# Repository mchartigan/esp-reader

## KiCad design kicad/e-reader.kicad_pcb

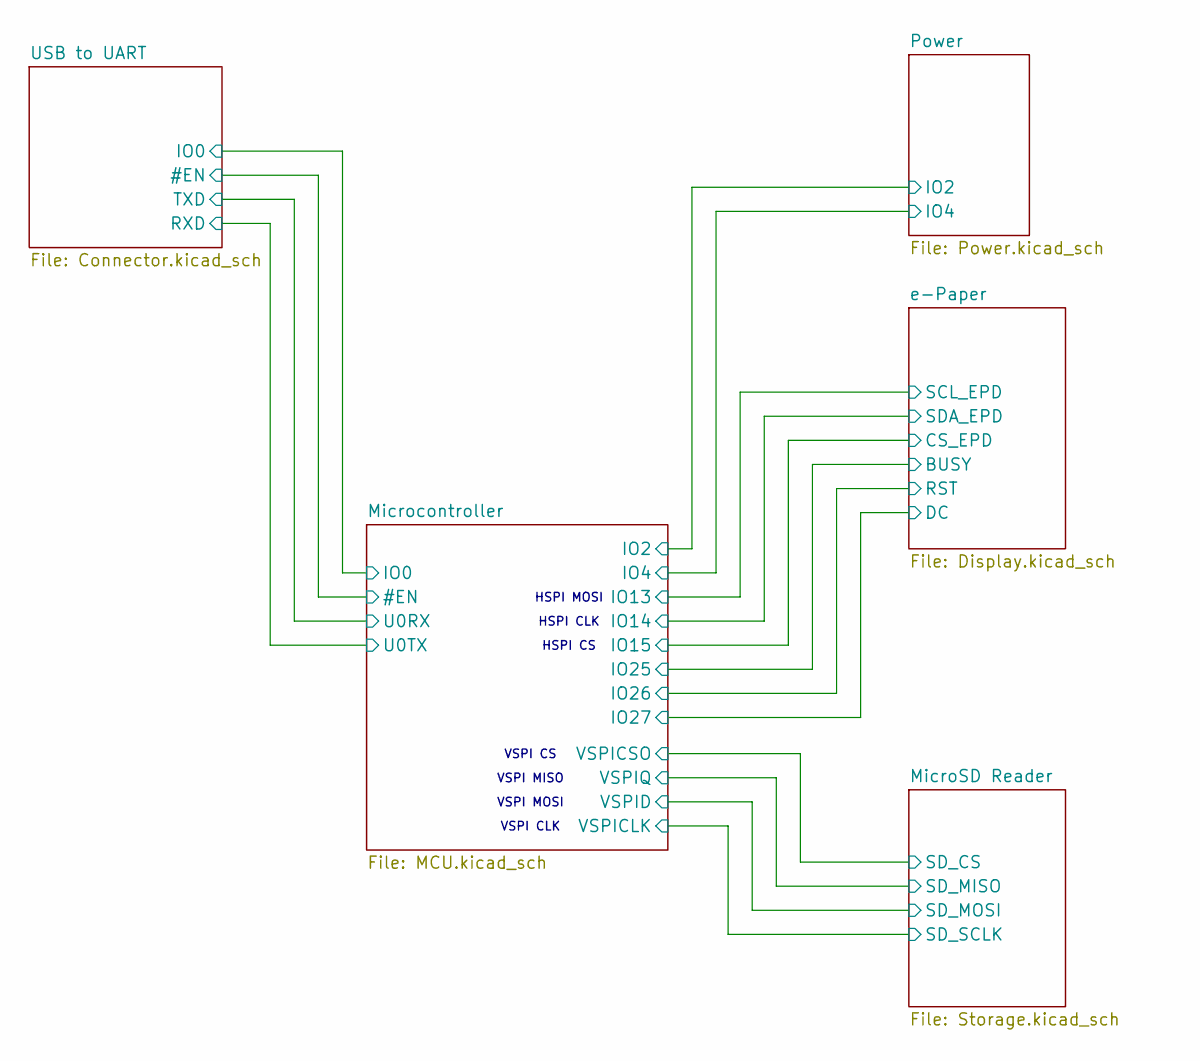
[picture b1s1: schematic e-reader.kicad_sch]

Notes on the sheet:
VSPI CS
VSPI CLK
HSPI CS
VSPI MOSI
HSPI CLK
HSPI MOSI
VSPI MISO

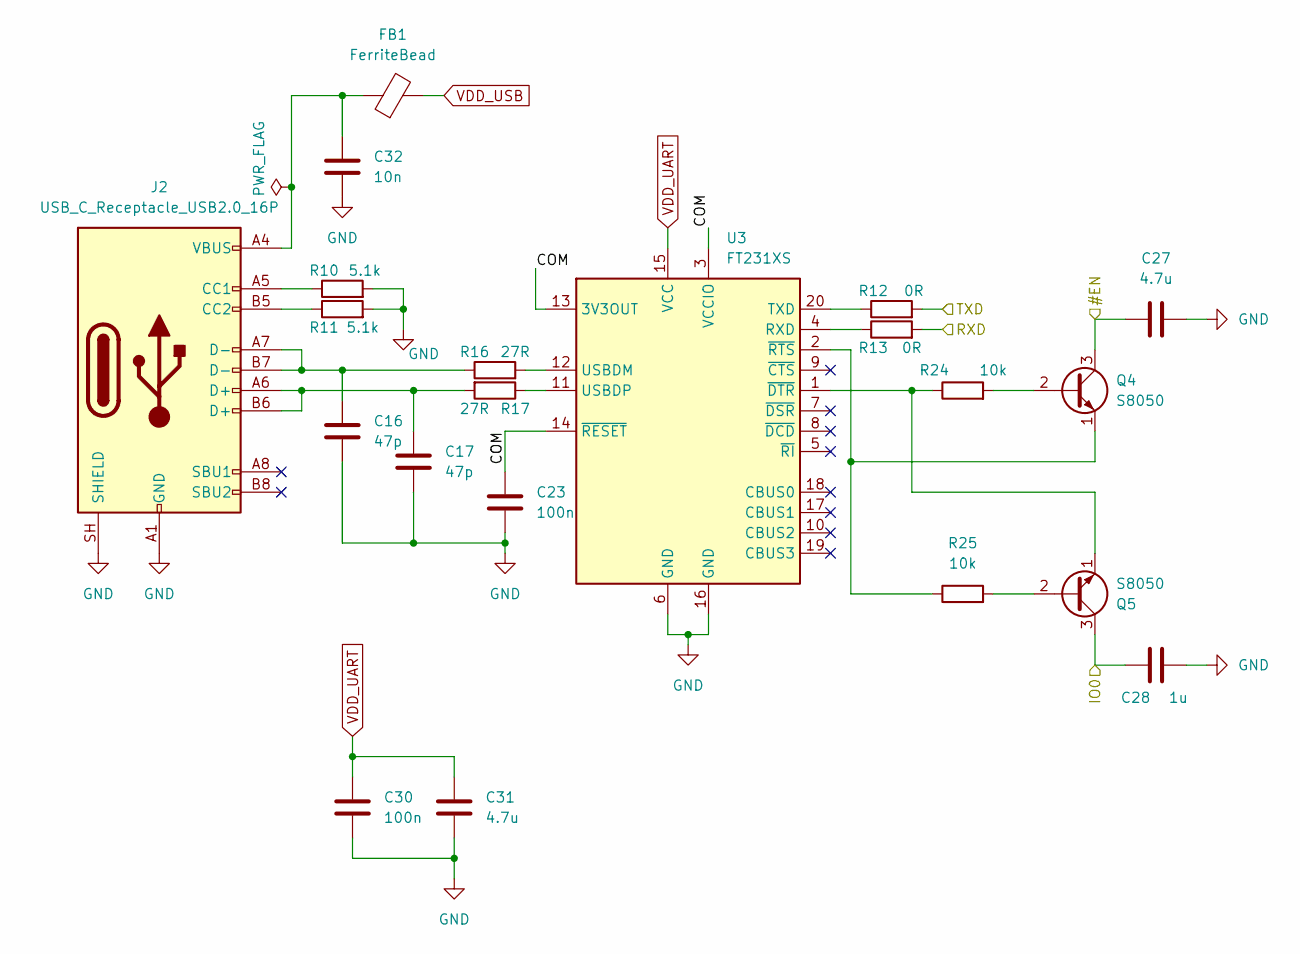
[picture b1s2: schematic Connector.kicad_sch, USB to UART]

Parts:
C16, C17: 47p; C_0603_1608Metric_Pad1.08x0.95mm_HandSolder
C23, C30: 100n; C_0603_1608Metric_Pad1.08x0.95mm_HandSolder
C27, C31: 4.7u; C_0603_1608Metric_Pad1.08x0.95mm_HandSolder
C28: 1u; C_0603_1608Metric_Pad1.08x0.95mm_HandSolder
C32: 10n; C_0603_1608Metric_Pad1.08x0.95mm_HandSolder
FB1: FerriteBead; R_0805_2012Metric_Pad1.20x1.40mm_HandSolder
J2: USB_C_Receptacle_USB2.0_16P; USB_C_Receptacle_GCT_USB4085
Q4, Q5: S8050; TO-92_Inline
R10, R11: 5.1k; R_0603_1608Metric_Pad0.98x0.95mm_HandSolder
R12, R13: 0R; R_0603_1608Metric_Pad0.98x0.95mm_HandSolder
R16, R17: 27R; R_0603_1608Metric_Pad0.98x0.95mm_HandSolder
R24, R25: 10k; R_0603_1608Metric_Pad0.98x0.95mm_HandSolder
U3: FT231XS; SSOP-20_3.9x8.7mm_P0.635mm

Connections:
/Microcontroller/FL_1: C28.1, Q5.3 (C); also elsewhere on the board
/Microcontroller/RST_1: C27.1, Q4.3 (C); also elsewhere on the board
/Microcontroller/U0RX: R12.2; also elsewhere on the board
/Microcontroller/U0TX: R13.2; also elsewhere on the board
/USB to UART/COM: C23.1, U3.3 (VCCIO), U3.13 (3V3OUT), U3.14 (~RESET)
GND: C16.2, C17.2, C23.2, C27.2, C28.2, C30.2, C31.2, C32.2, J2.A1 (GND), J2.A12 (GND), J2.B1 (GND), J2.B12 (GND), J2.SH (SHIELD), R10.2, R11.2, U3.6 (GND), U3.16 (GND); also elsewhere on the board
unnamed: C16.1, J2.A7 (D-), J2.B7 (D-), R16.1
unnamed: C17.1, J2.A6 (D+), J2.B6 (D+), R17.2
unnamed: C32.1, FB1.1, J2.A4 (VBUS), J2.A9 (VBUS), J2.B4 (VBUS), J2.B9 (VBUS)
unnamed: J2.A5 (CC1), R10.1
unnamed: J2.B5 (CC2), R11.1
unnamed: Q4.2 (B), R24.2
unnamed: Q4.1 (E), R25.1, U3.2 (~RTS)
unnamed: Q5.2 (B), R25.2
unnamed: Q5.1 (E), R24.1, U3.1 (~DTR)
unnamed: R13.1, U3.4 (RXD)
unnamed: R12.1, U3.20 (TXD)
unnamed: R16.2, U3.12 (USBDM)
unnamed: R17.1, U3.11 (USBDP)
VDD_UART: C30.1, C31.1, U3.15 (VCC); also elsewhere on the board
VDD_USB: FB1.2; also elsewhere on the board

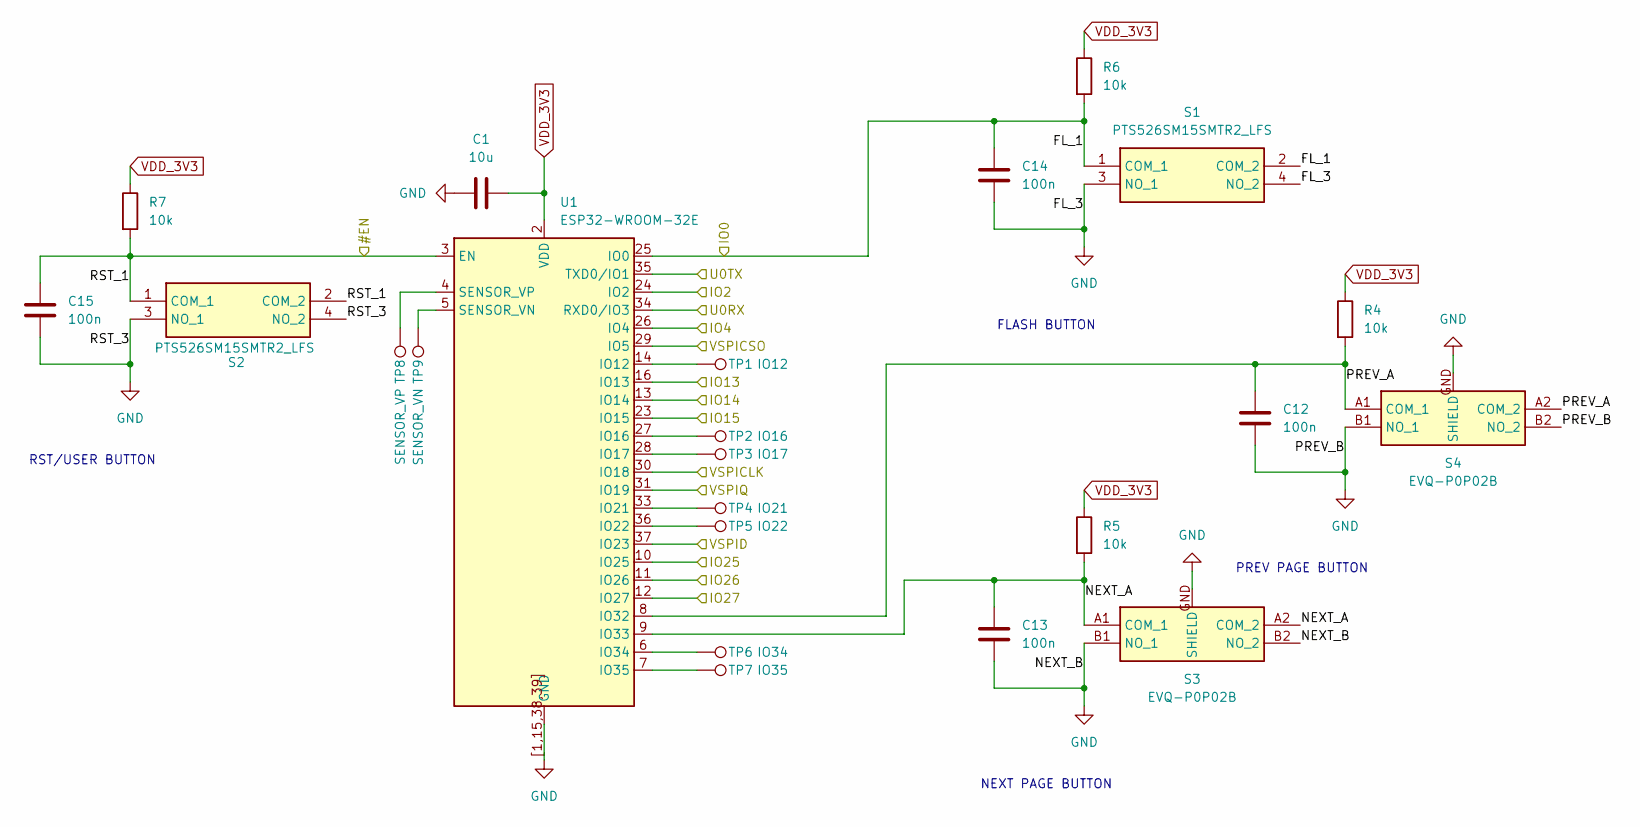
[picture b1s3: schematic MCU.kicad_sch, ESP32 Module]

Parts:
C1: 10u; C_0603_1608Metric_Pad1.08x0.95mm_HandSolder
C12, C13, C14, C15: 100n; C_0603_1608Metric_Pad1.08x0.95mm_HandSolder
R4, R5, R6, R7: 10k; R_0603_1608Metric_Pad0.98x0.95mm_HandSolder
S1, S2: PTS526SM15SMTR2_LFS; PTS526SM15SMTR2LFS; Manufacturer_Part_Number PTS526SM15SMTR2 LFS; Mouser Part Number 611-PTS526SM15SMTR2L
S3, S4: EVQ-P0P02B; EVQP0P02B; Manufacturer_Part_Number EVQ-P0P02B; Mouser Part Number 667-EVQ-P0P02B
TP1: IO12; TestPoint_THTPad_D2.0mm_Drill1.0mm
TP2: IO16; TestPoint_THTPad_D2.0mm_Drill1.0mm
TP3: IO17; TestPoint_THTPad_D2.0mm_Drill1.0mm
TP4: IO21; TestPoint_THTPad_D2.0mm_Drill1.0mm
TP5: IO22; TestPoint_THTPad_D2.0mm_Drill1.0mm
TP6: IO34; TestPoint_THTPad_D2.0mm_Drill1.0mm
TP7: IO35; TestPoint_THTPad_D2.0mm_Drill1.0mm
TP8: SENSOR_VP; TestPoint_THTPad_D2.0mm_Drill1.0mm
TP9: SENSOR_VN; TestPoint_THTPad_D2.0mm_Drill1.0mm
U1: ESP32-WROOM-32E

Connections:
/MicroSD Reader/SD_CS: U1.29 (IO5); also elsewhere on the board
/MicroSD Reader/SD_MISO: U1.31 (IO19); also elsewhere on the board
/MicroSD Reader/SD_MOSI: U1.37 (IO23); also elsewhere on the board
/MicroSD Reader/SD_SCLK: U1.30 (IO18); also elsewhere on the board
/Microcontroller/FL_1: C14.1, R6.2, S1.1 (COM_1), S1.2 (COM_2), U1.25 (IO0); also elsewhere on the board
/Microcontroller/IO2: U1.24 (IO2); also elsewhere on the board
/Microcontroller/IO4: U1.26 (IO4); also elsewhere on the board
/Microcontroller/IO13: U1.16 (IO13); also elsewhere on the board
/Microcontroller/IO14: U1.13 (IO14); also elsewhere on the board
/Microcontroller/IO15: U1.23 (IO15); also elsewhere on the board
/Microcontroller/IO25: U1.10 (IO25); also elsewhere on the board
/Microcontroller/IO26: U1.11 (IO26); also elsewhere on the board
/Microcontroller/IO27: U1.12 (IO27); also elsewhere on the board
/Microcontroller/NEXT_A: C13.1, R5.2, S3.A1 (COM_1), S3.A2 (COM_2), U1.9 (IO33)
/Microcontroller/PREV_A: C12.1, R4.2, S4.A1 (COM_1), S4.A2 (COM_2), U1.8 (IO32)
/Microcontroller/RST_1: C15.1, R7.2, S2.1 (COM_1), S2.2 (COM_2), U1.3 (EN); also elsewhere on the board
/Microcontroller/U0RX: U1.34 (RXD0/IO3); also elsewhere on the board
/Microcontroller/U0TX: U1.35 (TXD0/IO1); also elsewhere on the board
GND: C1.1, C12.2, C13.2, C14.2, C15.2, S1.3 (NO_1), S1.4 (NO_2), S2.3 (NO_1), S2.4 (NO_2), S3.B1 (NO_1), S3.B2 (NO_2), S3.GND (SHIELD), S4.B1 (NO_1), S4.B2 (NO_2), S4.GND (SHIELD), U1.1 (GND), U1.15 (GND), U1.38 (GND), U1.39 (GND), U1.[1,15,38,39] (GND); also elsewhere on the board
unnamed: TP1.1 (1_1), U1.14 (IO12)
unnamed: TP2.1 (1_1), U1.27 (IO16)
unnamed: TP3.1 (1_1), U1.28 (IO17)
unnamed: TP4.1 (1_1), U1.33 (IO21)
unnamed: TP5.1 (1_1), U1.36 (IO22)
unnamed: TP6.1 (1_1), U1.6 (IO34)
unnamed: TP7.1 (1_1), U1.7 (IO35)
unnamed: TP9.1 (1_1), U1.5 (SENSOR_VN)
unnamed: TP8.1 (1_1), U1.4 (SENSOR_VP)
VDD_3V3: C1.2, R4.1, R5.1, R6.1, R7.1, U1.2 (VDD); also elsewhere on the board

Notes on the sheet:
RST/USER BUTTON
NEXT PAGE BUTTON
FLASH BUTTON
PREV PAGE BUTTON

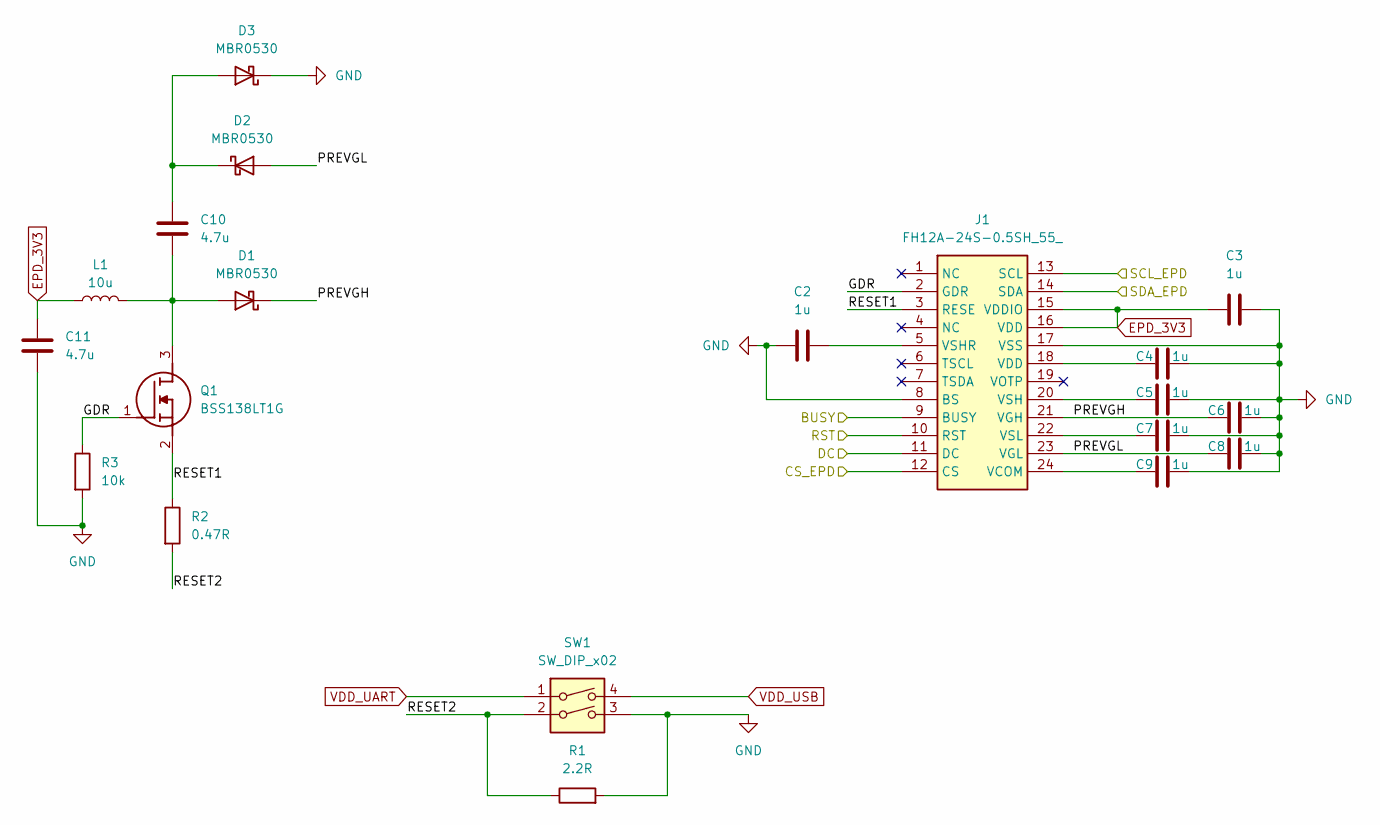
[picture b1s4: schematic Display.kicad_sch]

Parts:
C2, C3, C4, C5, C6, C7, C8, C9: 1u; C_0603_1608Metric_Pad1.08x0.95mm_HandSolder; Voltage 50V
C10: 4.7u; C_0603_1608Metric_Pad1.08x0.95mm_HandSolder; Voltage 50V
C11: 4.7u; C_0603_1608Metric_Pad1.08x0.95mm_HandSolder
D1, D2, D3: MBR0530; D_SOD-123
J1: FH12A-24S-0.5SH_55_; FH12A-24S-0.5SH; Manufacturer_Part_Number FH12A-24S-0.5SH(55); Mouser Part Number 798-FH12A-24S0.5SH55
L1: 10u; SRN4012BTA100M
Q1: BSS138LT1G; Manufacturer_Part_Number BSS138LT1G; Mouser Part Number 863-BSS138LT1G
R1: 2.2R; R_0603_1608Metric_Pad0.98x0.95mm_HandSolder
R2: 0.47R; R_0603_1608Metric_Pad0.98x0.95mm_HandSolder
R3: 10k; R_0603_1608Metric_Pad0.98x0.95mm_HandSolder
SW1: SW_DIP_x02; 2182LPST

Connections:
/Microcontroller/IO13: J1.13 (SCL); also elsewhere on the board
/Microcontroller/IO14: J1.14 (SDA); also elsewhere on the board
/Microcontroller/IO15: J1.12 (CS); also elsewhere on the board
/Microcontroller/IO25: J1.9 (BUSY); also elsewhere on the board
/Microcontroller/IO26: J1.10 (RST); also elsewhere on the board
/Microcontroller/IO27: J1.11 (DC); also elsewhere on the board
/e-Paper/GDR: J1.2 (GDR), Q1.1 (G), R3.1
/e-Paper/PREVGH: C6.1, D1.1 (K), J1.21 (VGH)
/e-Paper/PREVGL: C8.1, D2.2 (A), J1.23 (VGL)
/e-Paper/RESET1: J1.3 (RESE), Q1.2 (S), R2.1
/e-Paper/RESET2: R1.1, R2.2, SW1.2
EPD_3V3: C3.1, C11.1, J1.15 (VDDIO), J1.16 (VDD), L1.1; also elsewhere on the board
GND: C2.1, C3.2, C4.2, C5.2, C6.2, C7.2, C8.2, C9.2, C11.2, D3.1 (K), J1.8 (BS), J1.17 (VSS), R1.2, R3.2, SW1.3; also elsewhere on the board
unnamed: C4.1, J1.18 (VDD)
unnamed: C10.2, D1.2 (A), L1.2, Q1.3 (D)
unnamed: C10.1, D2.1 (K), D3.2 (A)
unnamed: C9.1, J1.24 (VCOM)
unnamed: C5.1, J1.20 (VSH)
unnamed: C2.2, J1.5 (VSHR)
unnamed: C7.1, J1.22 (VSL)
VDD_UART: SW1.1; also elsewhere on the board
VDD_USB: SW1.4; also elsewhere on the board

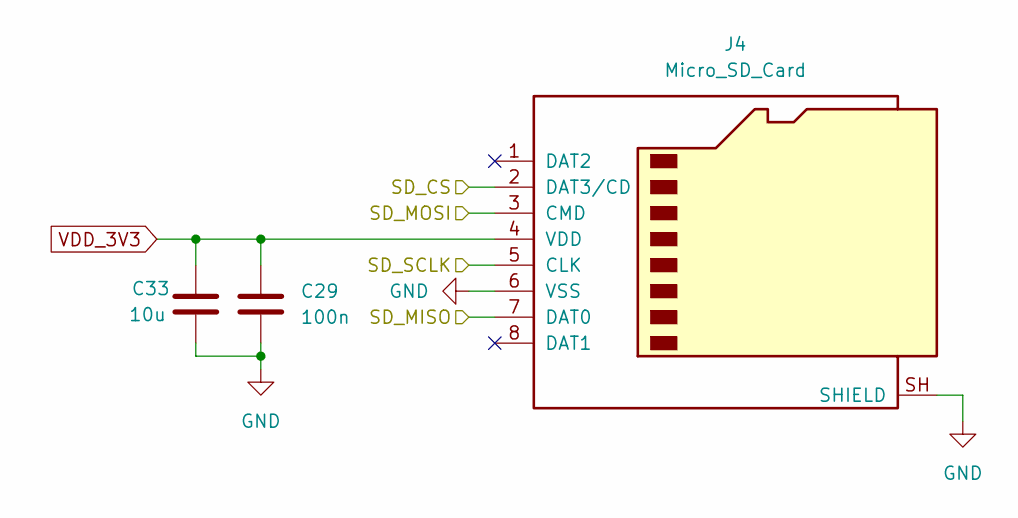
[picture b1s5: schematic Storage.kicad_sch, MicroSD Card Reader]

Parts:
C29: 100n; C_0603_1608Metric_Pad1.08x0.95mm_HandSolder
C33: 10u; C_0603_1608Metric_Pad1.08x0.95mm_HandSolder
J4: Micro_SD_Card; microSD_HC_Hirose_DM3AT-SF-PEJM5

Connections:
/MicroSD Reader/SD_CS: J4.2 (DAT3/CD); also elsewhere on the board
/MicroSD Reader/SD_MISO: J4.7 (DAT0); also elsewhere on the board
/MicroSD Reader/SD_MOSI: J4.3 (CMD); also elsewhere on the board
/MicroSD Reader/SD_SCLK: J4.5 (CLK); also elsewhere on the board
GND: C29.2, C33.2, J4.6 (VSS), J4.SH (SHIELD); also elsewhere on the board
VDD_3V3: C29.1, C33.1, J4.4 (VDD); also elsewhere on the board

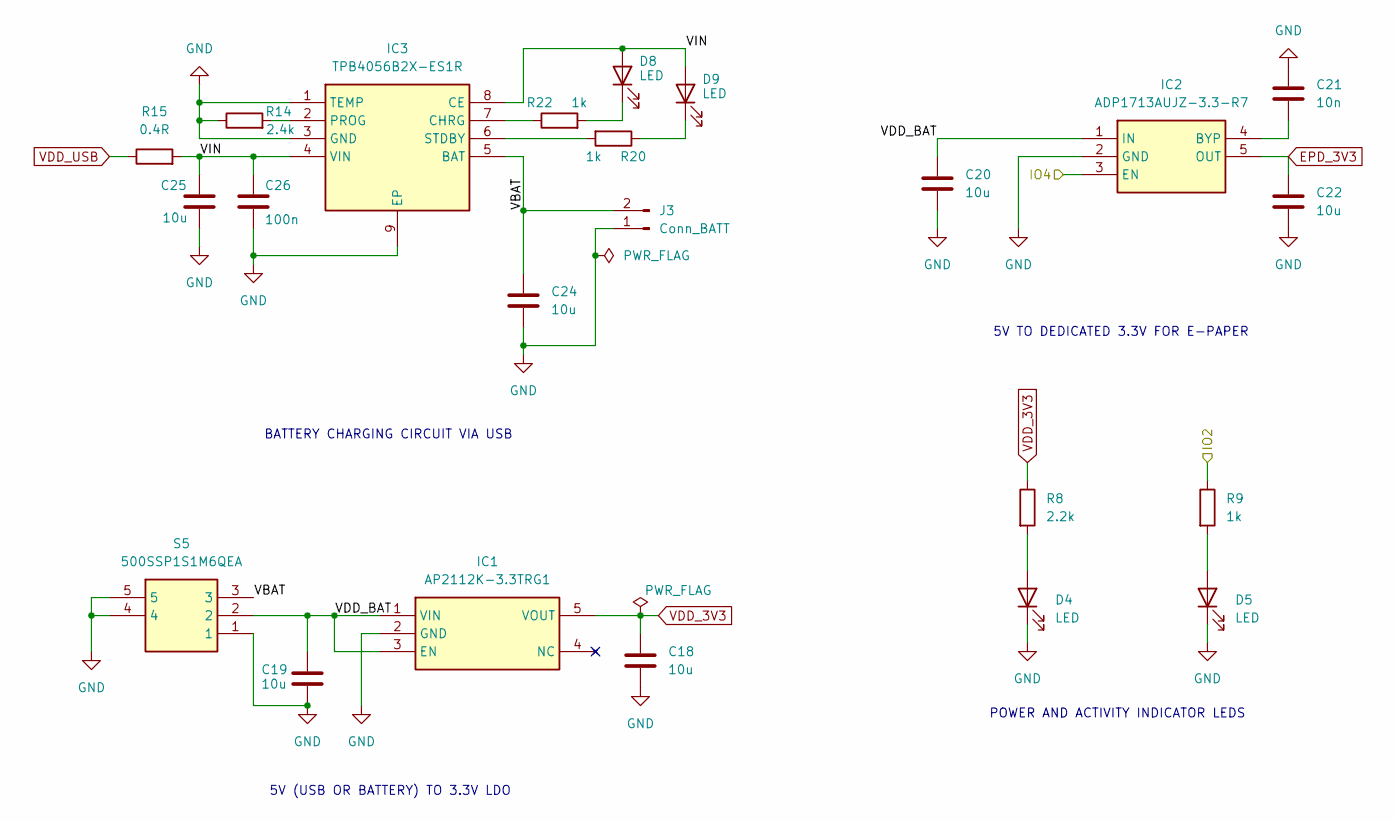
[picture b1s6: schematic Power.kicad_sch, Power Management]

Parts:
C18, C19, C20, C22, C24, C25: 10u; C_0603_1608Metric_Pad1.08x0.95mm_HandSolder
C21: 10n; C_0603_1608Metric_Pad1.08x0.95mm_HandSolder
C26: 100n; C_0603_1608Metric_Pad1.08x0.95mm_HandSolder
D4, D5, D8, D9: LED; LED_0805_2012Metric_Pad1.15x1.40mm_HandSolder
IC1: AP2112K-3.3TRG1; SOT-23-5; Manufacturer_Part_Number AP2112K-3.3TRG1; Mouser Part Number 621-AP2112K-3.3TRG1
IC2: ADP1713AUJZ-3.3-R7; TSOT-23-5; Manufacturer_Part_Number ADP1713AUJZ-3.3-R7; Mouser Part Number 584-ADP1713AUJZ3.3R7
IC3: TPB4056B2X-ES1R; Manufacturer_Part_Number TPB4056B2X-ES1R
J3: Conn_BATT; WireHeader_1x02_D1.00mm
R8: 2.2k; R_0603_1608Metric_Pad0.98x0.95mm_HandSolder
R9, R20, R22: 1k; R_0603_1608Metric_Pad0.98x0.95mm_HandSolder
R14: 2.4k; R_0603_1608Metric_Pad0.98x0.95mm_HandSolder
R15: 0.4R; R_1206_3216Metric_Pad1.30x1.75mm_HandSolder
S5: 500SSP1S1M6QEA; Manufacturer_Part_Number 500SSP1S1M6QEA; Mouser Part Number 612-500-A161

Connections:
/Microcontroller/IO2: R9.1; also elsewhere on the board
/Microcontroller/IO4: IC2.3 (EN); also elsewhere on the board
/Power/VBAT: C24.1, IC3.5 (BAT), J3.2, S5.3
/Power/VDD_BAT: C19.1, C20.1, IC1.1 (VIN), IC1.3 (EN), IC2.1 (IN), S5.2
/Power/VIN: C25.1, C26.1, D8.2 (A), D9.2 (A), IC3.4 (VIN), IC3.8 (CE), R15.2
EPD_3V3: C22.1, IC2.5 (OUT); also elsewhere on the board
GND: C18.2, C19.2, C20.2, C21.1, C22.2, C24.2, C25.2, C26.2, D4.1 (K), D5.1 (K), IC1.2 (GND), IC2.2 (GND), IC3.1 (TEMP), IC3.3 (GND), IC3.9 (EP), J3.1, R14.1, S5.1, S5.4, S5.5; also elsewhere on the board
unnamed: D4.2 (A), R8.2
unnamed: D5.2 (A), R9.2
unnamed: D8.1 (K), R22.2
unnamed: D9.1 (K), R20.1
unnamed: C21.2, IC2.4 (BYP)
unnamed: IC3.7 (CHRG), R22.1
unnamed: IC3.2 (PROG), R14.2
unnamed: IC3.6 (STDBY), R20.2
VDD_3V3: C18.1, IC1.5 (VOUT), R8.1; also elsewhere on the board
VDD_USB: R15.1; also elsewhere on the board

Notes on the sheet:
5V (USB OR BATTERY) TO 3.3V LDO
POWER AND ACTIVITY INDICATOR LEDS
BATTERY CHARGING CIRCUIT VIA USB
5V TO DEDICATED 3.3V FOR E-PAPER

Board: 2 copper layers, 90 parts (0 on the bottom side), 69 nets, no tracks yet.
